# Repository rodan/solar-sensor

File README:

Solar sensor device that implements the following:

   - read temperature, humidity, pressure and geiger counter sensors
   - read thermocouple temperature
   - read and set alarms in the real time clock
   - log sensor data on a microSD card
   - control room heating or cooling via RF power switches
   - use a communication protocol to send data to a PC

  there are 4 components in this repository:
  firmware_arduino  - contains the Arduino source code (avr version)
  firmware_avr      - stand-alone source code (avr version)
  hardware_avr      - open source hardware for the main board (avr version)
  server            - server-side implementation of the comm protocol

  pictures of rev02 and rev03 are available at 
            https://picasaweb.google.com/petre.rodan/SolarSensor

  Library dependencies for firmware_arduino software:

  ds3231      https://github.com/rodan/ds3231
  max6675     https://github.com/rodan/max6675
  bmp085      https://github.com/rodan/bmp085
  sht15       http://www.arduino.cc/playground/Code/Sensirion
  IRremote    https://github.com/shirriff/Arduino-IRremote
  SDfatlib    http://code.google.com/p/sdfatlib/

  dependencies for the server-side software:

  linux with working ftdi kernel driver
  sqlite      http://www.sqlite.org/
  gnuplot     http://www.gnuplot.info/

  Hardware needed:

  SHT15 Humidity and Temperature Sensor  - sparkfun sku: SEN-08257
  Grove - Geiger Counter - seeed studio sku: SEN63024P
  3W Solar Panel  - seeed studio sku: POW92136O
  Lithium Ion polymer Battery - 2Ah 3.7V  - seeed studio sku: POW103C1P
  XBee 2mW Chip Antenna - Series 2 ZigBee (2 pcs)  - sparkfun sku: WRL-10415
  XBee Explorer USB  - sparkfun sku: WRL-08687
  main board that includes the LiPo charger, DS3231 to wake up the system, 
    5v boost, one logic level converter, 3.3v stabilized sources, atmega328p uC, 
    uSD card socket, xbee socket, digital cold junction compensated K-type 
    thermocouple IC and mosfets to power off unused modules.

  How does it work

    Power: the main power is from a 2Ah LiPo cell that is charged from the solar panel. a stabilization circuit and a boost give out 3.3V and 5V respectively. a small coin cell battery keeps the DS3231 RTC chip working at all times. the RTC's alarm function is waking up the microcontroller once every 30 minutes.

    Sensors: some are internal and some kept outside. The outside temperature and humidity are measured by a SHT15 chip. the Geiger-Muller tube is also kept outside. the internal temperature is read from the RTC chip, or via a K-type thermocouple.

    Sensor data: is saved to a uSD card and if the receiving PC is up and if the wireless signal haven't got too much interference than a protocol is used to send new data to the PC. it ends up here: http://www.simplex.ro/ro/statie_meteo.html

    Commands: are being given either via the wireless serial interface or via a universal remote control that can speak RC5 (most remotes can).

  Author:          Petre Rodan <2b4eda@subdimension.ro>
  Available from:  https://github.com/rodan/solar-sensor
  License:         GNU GPLv3

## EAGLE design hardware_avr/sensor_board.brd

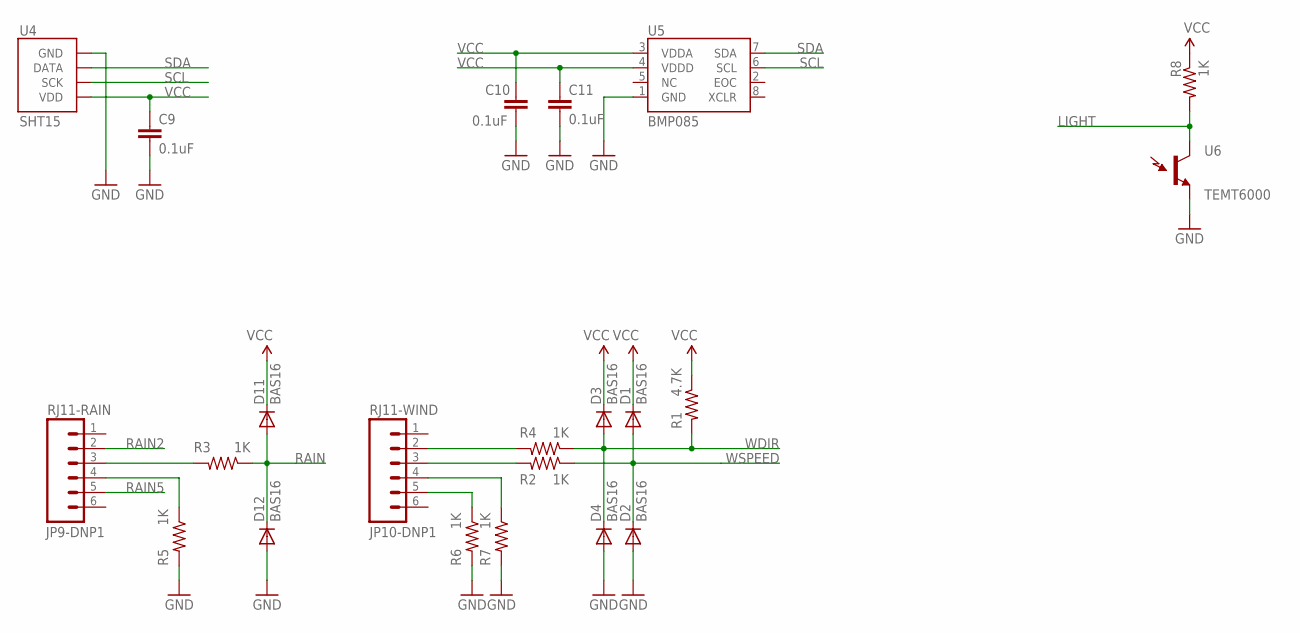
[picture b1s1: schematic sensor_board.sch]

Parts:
C9, C10, C11: 0.1uF; 0402-CAP
D1, D2, D3, D4, D11, D12: BAS16; SOD-323
JP9-DNP1: RJ11-RAIN; RJ11-6
JP10-DNP1: RJ11-WIND; RJ11-6
R1: 4.7K; 0402-RES
R2, R3, R4, R5, R6, R7, R8: 1K; 0402-RES
U4: SHT15; SHT1X
U5: BMP085
U6: TEMT6000; TEMT6000-SEN

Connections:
GND: C9.2, C10.1, C11.2, D2.2 (A), D4.2 (A), D12.2 (A), R5.2, R6.2, R7.2, U4.1 (GND), U5.1 (GND), U6.EMITTER (E1)
LIGHT: R8.2, U6.COLLECTOR (C1)
unnamed: JP10-DNP1.2, R4.2
unnamed: JP10-DNP1.3, R2.2
unnamed: JP9-DNP1.3, R3.2
unnamed: JP9-DNP1.4, R5.1
unnamed: JP10-DNP1.5, R6.1
unnamed: JP10-DNP1.4, R7.1
RAIN: D11.2 (A), D12.1 (C), R3.1
RAIN2: JP9-DNP1.2
RAIN5: JP9-DNP1.5
SCL: U4.3 (SCK), U5.6 (SCL)
SDA: U4.2 (DATA), U5.7 (SDA)
VCC: C9.1, C10.2, C11.1, D1.1 (C), D3.1 (C), D11.1 (C), R1.1, R8.1, U4.4 (VDD), U5.3 (VDDA), U5.4 (VDDD)
WDIR: D3.2 (A), D4.1 (C), R1.2, R4.1
WSPEED: D1.2 (A), D2.1 (C), R2.1

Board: 2 copper layers, 22 parts (0 on the bottom side), 14 nets, no tracks yet.

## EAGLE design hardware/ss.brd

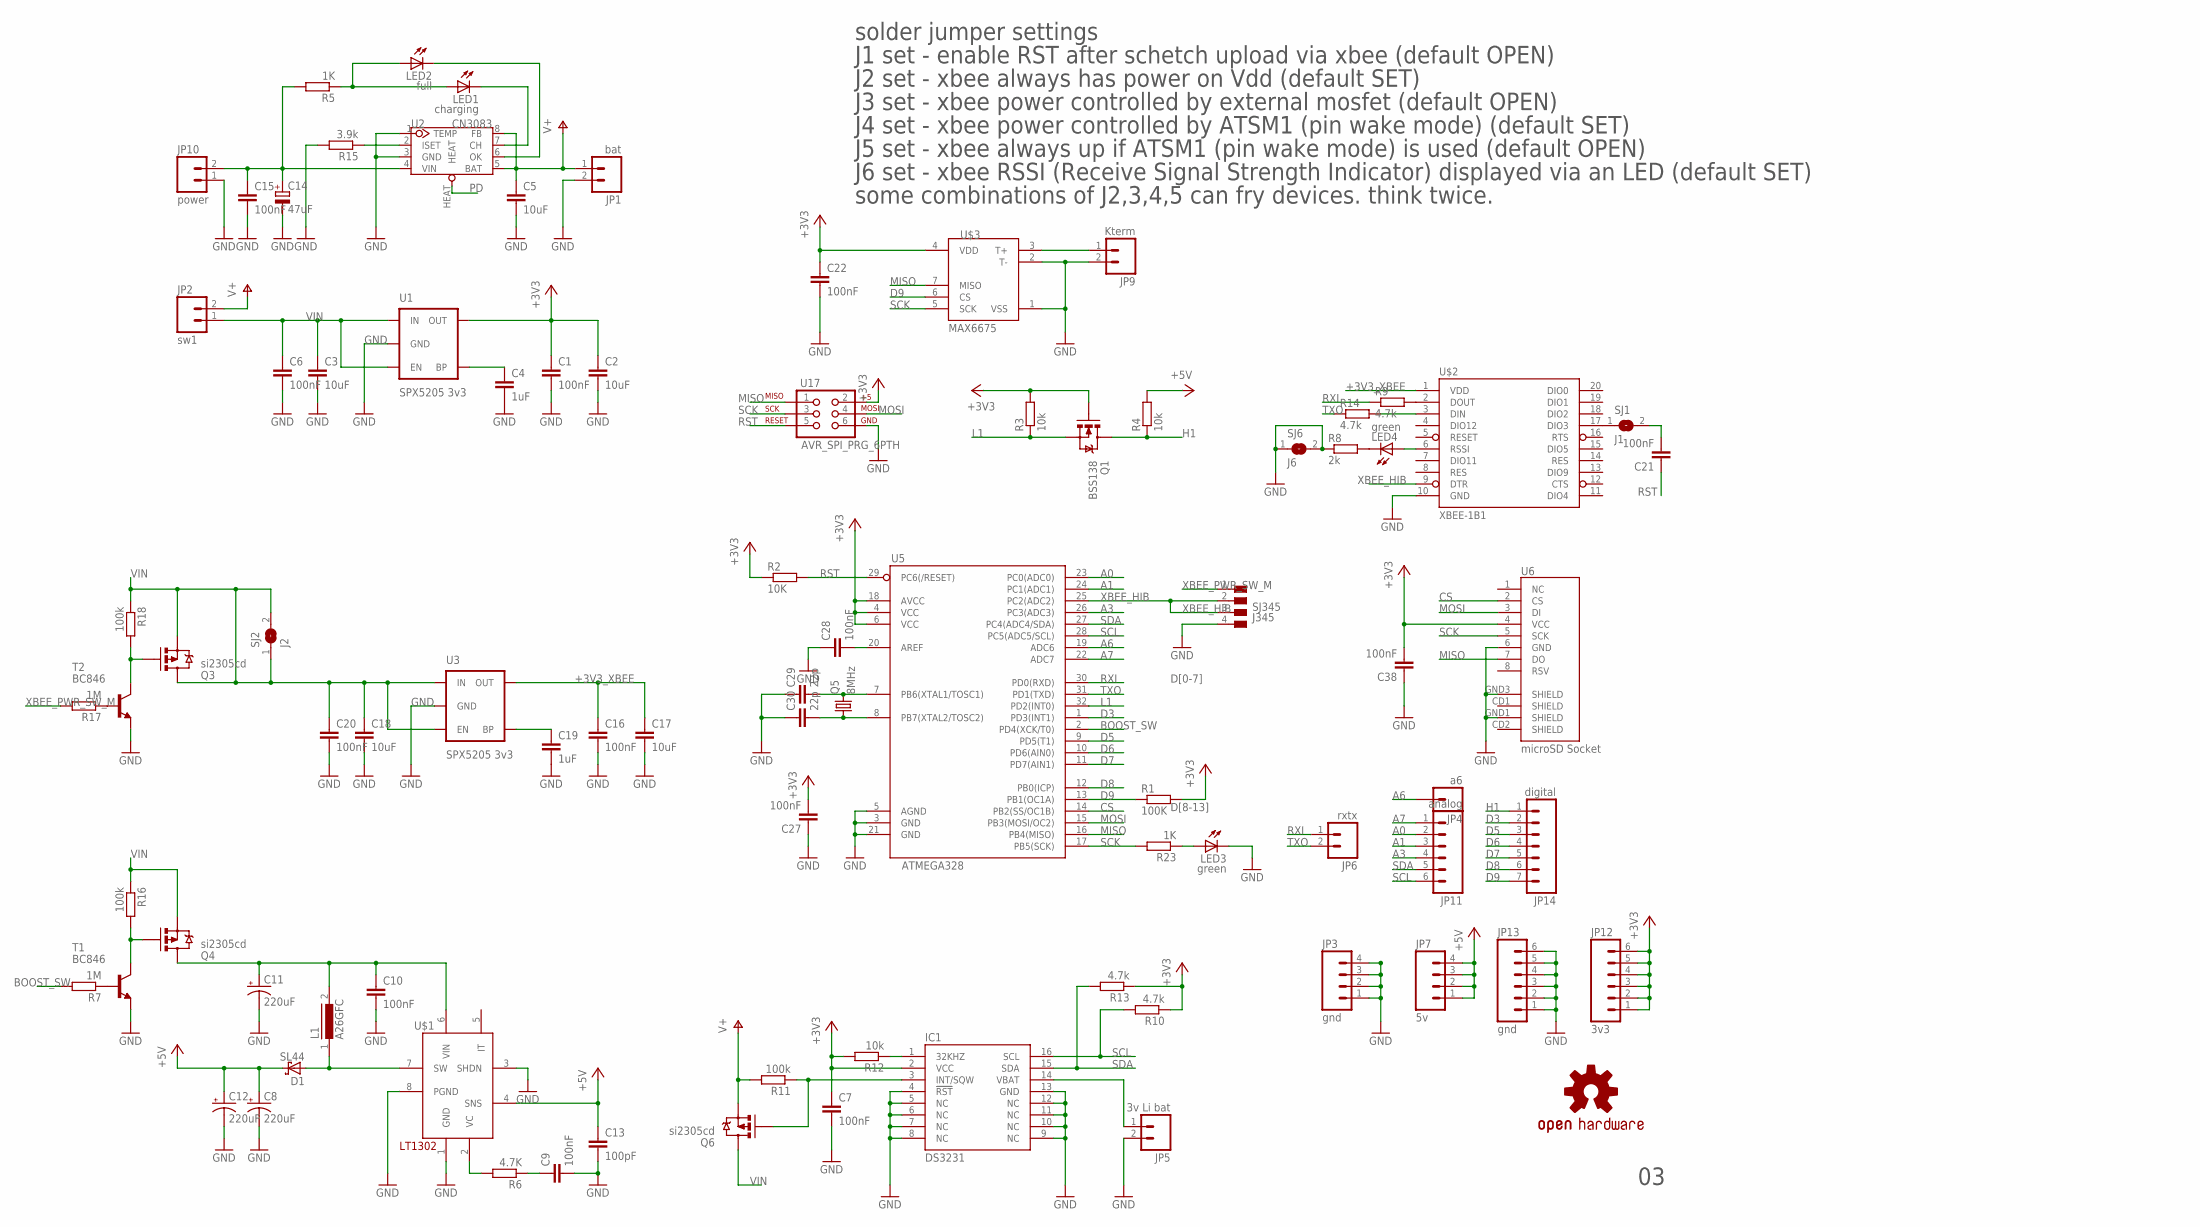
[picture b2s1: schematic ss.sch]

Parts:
C1, C6, C7, C9, C10, C15, C16, C20, C21, C22, C27, C28, C38: 100nF; C0805
C2, C3, C5, C17, C18: 10uF; C1206
C4, C19: 1uF; C0805
C8, C11, C12: 220uF; PANASONIC_D
C13: 100pF; C0805
C14: 47uF; CT7343
C29, C30: 22p; C0805
D1: SL44; SMC
IC1: DS3231; SO-16
JP1: bat; 1X02
JP2: sw1; 1X02
JP3: gnd; 1X04
JP4: a6; 1X01
JP5: 3v Li bat; 1X02
JP6: rxtx; 1X02
JP7: 5v; 1X04
JP9: Kterm; 1X02
JP10: power; 1X02
JP11: analog; 1X06
JP12: 3v3; 1X06
JP13: gnd; 1X06
JP14: digital; 1X07
L1: A26GFC
LED1: charging; CHIP-LED0805
LED2: full; CHIP-LED0805
LED3, LED4: green; CHIP-LED0805
Q1: BSS138; SOT23-3
Q3, Q4, Q6: si2305cd; SOT23-3_POWER
Q5: 8MHz; CRYSTAL_5X3.2
R1: 100K; R0805W
R2: 10K; R0805W
R3, R4, R12: 10k; R0805W
R5, R23: 1K; R0805W
R6: 4.7K; R0805W
R7, R17: 1M; R0805W
R8: 2k; R0805W
R9, R10, R13, R14: 4.7k; R0805W
R11, R16, R18: 100k; R0805W
R15: 3.9k; R0805W
SJ1: J1; SJ
SJ2: J2; SJ
SJ6: J6; SJ
SJ345: J345; SJ_4P
T1, T2: BC846; SOT23
U1, U3: SPX5205 3v3; SOT23-5
U2: CN3083; SOP8-W/-HEAT
U5: ATMEGA328; TQFP32-08
U6: microSD Socket; MICRO-SD-SOCKET-PP
U17: AVR_SPI_PRG_6PTH; 2X3
U$1: LT1302SOIC8; SO08
U$2: XBEE-1B1; XBEE-1
U$3: MAX6675; SO08-MAX6675
U$7: OSHW-LOGOM; OSHW-LOGO-M

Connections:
+3V3: C1.1, C2.1, C7.1, C22.1, C27.2, C38.2, IC1.2 (VCC), JP12.1, JP12.2, JP12.3, JP12.4, JP12.5, JP12.6, Q1.1 (G), R1.2, R2.1, R3.2, R10.1, R12.2, R13.1, U1.5 (OUT), U5.4 (VCC), U5.6 (VCC), U5.18 (AVCC), U6.4 (VCC), U17.2, U$3.4 (VDD)
+3V3_XBEE: C16.1, C17.1, U3.5 (OUT), U$2.1 (VDD)
+5V: C8.+, C12.+, C13.1, D1.C, JP7.1, JP7.2, JP7.3, JP7.4, R4.2, U$1.4 (SNS)
A0: JP11.2, U5.23 (PC0(ADC0))
A1: JP11.3, U5.24 (PC1(ADC1))
A3: JP11.4, U5.26 (PC3(ADC3))
A6: JP4.1, U5.19 (ADC6)
A7: JP11.1, U5.22 (ADC7)
BOOST_IN: C10.1, C11.+, L1.2, Q4.3 (D), U$1.6 (VIN)
BOOST_SW: R7.2, U5.2 (PD4(XCK/T0))
CS: U5.14 (PB2(SS/OC1B)), U6.2 (CS)
D3: JP14.2, U5.1 (PD3(INT1))
D5: JP14.3, U5.9 (PD5(T1))
D6: JP14.4, U5.10 (PD6(AIN0))
D7: JP14.5, U5.11 (PD7(AIN1))
D8: JP14.6, U5.12 (PB0(ICP))
D9: JP14.7, R1.1, U5.13 (PB1(OC1A)), U$3.6 (CS)
GND: C1.2, C2.2, C3.2, C4.2, C5.2, C6.2, C7.2, C8.-, C9.2, C10.2, C11.-, C12.-, C13.2, C14.-, C15.2, C16.2, C17.2, C18.2, C19.2, C20.2, C22.2, C27.1, C28.1, C29.1, C30.1, C38.1, IC1.4 (!RST), IC1.5 (NC), IC1.6 (NC), IC1.7 (NC), IC1.8 (NC), IC1.9 (NC), IC1.10 (NC), IC1.11 (NC), IC1.12 (NC), IC1.13 (GND), JP1.2, JP3.1, JP3.2, JP3.3, JP3.4, JP5.2, JP9.2, JP10.1, JP13.1, JP13.2, JP13.3, JP13.4, JP13.5, JP13.6, LED3.C, R8.1, R15.2, SJ6.1, SJ6.2, SJ345.4, T1.2 (E), T2.2 (E), U1.2 (GND), U2.1 (TEMP), U2.3 (GND), U3.2 (GND), U5.3 (GND), U5.5 (AGND), U5.21 (GND), U6.6 (GND), U6.GND1 (SHIELD), U6.GND3 (SHIELD), U17.6, U$1.1 (GND), U$1.3 (SHDN), U$1.8 (PGND), U$2.10 (GND), U$3.1 (VSS), U$3.2 (T-)
H1: JP14.1, Q1.3 (D), R4.1
L1: Q1.2 (S), R3.1, U5.32 (PD2(INT0))
MISO: U5.16 (PB4(MISO)), U6.7 (DO), U17.1, U$3.7 (MISO)
MOSI: U5.15 (PB3(MOSI/OC2)), U6.3 (DI), U17.4
unnamed: IC1.3 (INT/SQW), Q6.1 (G), R11.1
unnamed: C4.1, U1.4 (BP)
unnamed: D1.A, L1.1, U$1.7 (SW)
unnamed: SJ1.1, U$2.17 (DIO3)
unnamed: C19.1, U3.4 (BP)
unnamed: LED4.C, R8.2
unnamed: LED4.A, U$2.6 (RSSI)
unnamed: IC1.1 (32KHZ), R12.1
unnamed: R15.1, U2.2 (ISET)
unnamed: IC1.14 (VBAT), JP5.1
unnamed: R6.2, U$1.2 (VC)
unnamed: C14.+, C15.1, JP10.2, R5.2, U2.4 (VIN)
unnamed: C9.1, R6.1
unnamed: LED1.A, LED2.A, R5.1
unnamed: LED1.C, U2.7 (CH)
unnamed: LED2.C, U2.6 (OK)
unnamed: C21.2, SJ1.2
unnamed: R17.1, T2.1 (B)
unnamed: C30.2, Q5.P$1 (1), U5.8 (PB7(XTAL2/TOSC2))
unnamed: Q3.1 (G), R18.2, T2.3 (C)
unnamed: C29.2, Q5.P$2 (2), U5.7 (PB6(XTAL1/TOSC1))
unnamed: C28.2, U5.20 (AREF)
unnamed: R9.2, U$2.2 (DOUT)
unnamed: R14.2, U$2.3 (DIN)
unnamed: R7.1, T1.1 (B)
unnamed: Q4.1 (G), R16.2, T1.3 (C)
unnamed: LED3.A, R23.1
PD: U2.HEAT
RST: C21.1, R2.2, U5.29 (PC6(/RESET)), U17.5
RXI: JP6.1, R9.1, U5.30 (PD0(RXD))
SCK: R23.2, U5.17 (PB5(SCK)), U6.5 (SCK), U17.3, U$3.5 (SCK)
SCL: IC1.16 (SCL), JP11.6, R10.2, U5.28 (PC5(ADC5/SCL))
SDA: IC1.15 (SDA), JP11.5, R13.2, U5.27 (PC4(ADC4/SDA))
T+: JP9.1, U$3.3 (T+)
TXO: JP6.2, R14.1, U5.31 (PD1(TXD))
V+: C5.1, JP1.1, JP2.2, Q6.2 (S), R11.2, U2.5 (BAT), U2.8 (FB)
VIN: C3.1, C6.1, C18.1, C20.1, JP2.1, Q3.2 (S), Q3.3 (D), Q4.2 (S), Q6.3 (D), R16.1, R18.1, SJ2.1, SJ2.2, U1.1 (IN), U1.3 (EN), U3.1 (IN), U3.3 (EN)
XBEE_HIB: SJ345.2, SJ345.3, U5.25 (PC2(ADC2)), U$2.9 (DTR)
XBEE_PWR_SW_M: R17.2, SJ345.1

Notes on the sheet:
D[0-7]
D[8-13]
J1 set - enable RST after schetch upload via xbee (default OPEN)
J2 set - xbee always has power on Vdd (default SET)
solder jumper settings
J3 set - xbee power controlled by external mosfet (default OPEN)
J4 set - xbee power controlled by ATSM1 (pin wake mode) (default SET)
J5 set - xbee always up if ATSM1 (pin wake mode) is used (default OPEN)
J6 set - xbee RSSI (Receive Signal Strength Indicator) displayed via an LED (default SET)
some combinations of J2,3,4,5 can fry devices. think twice.

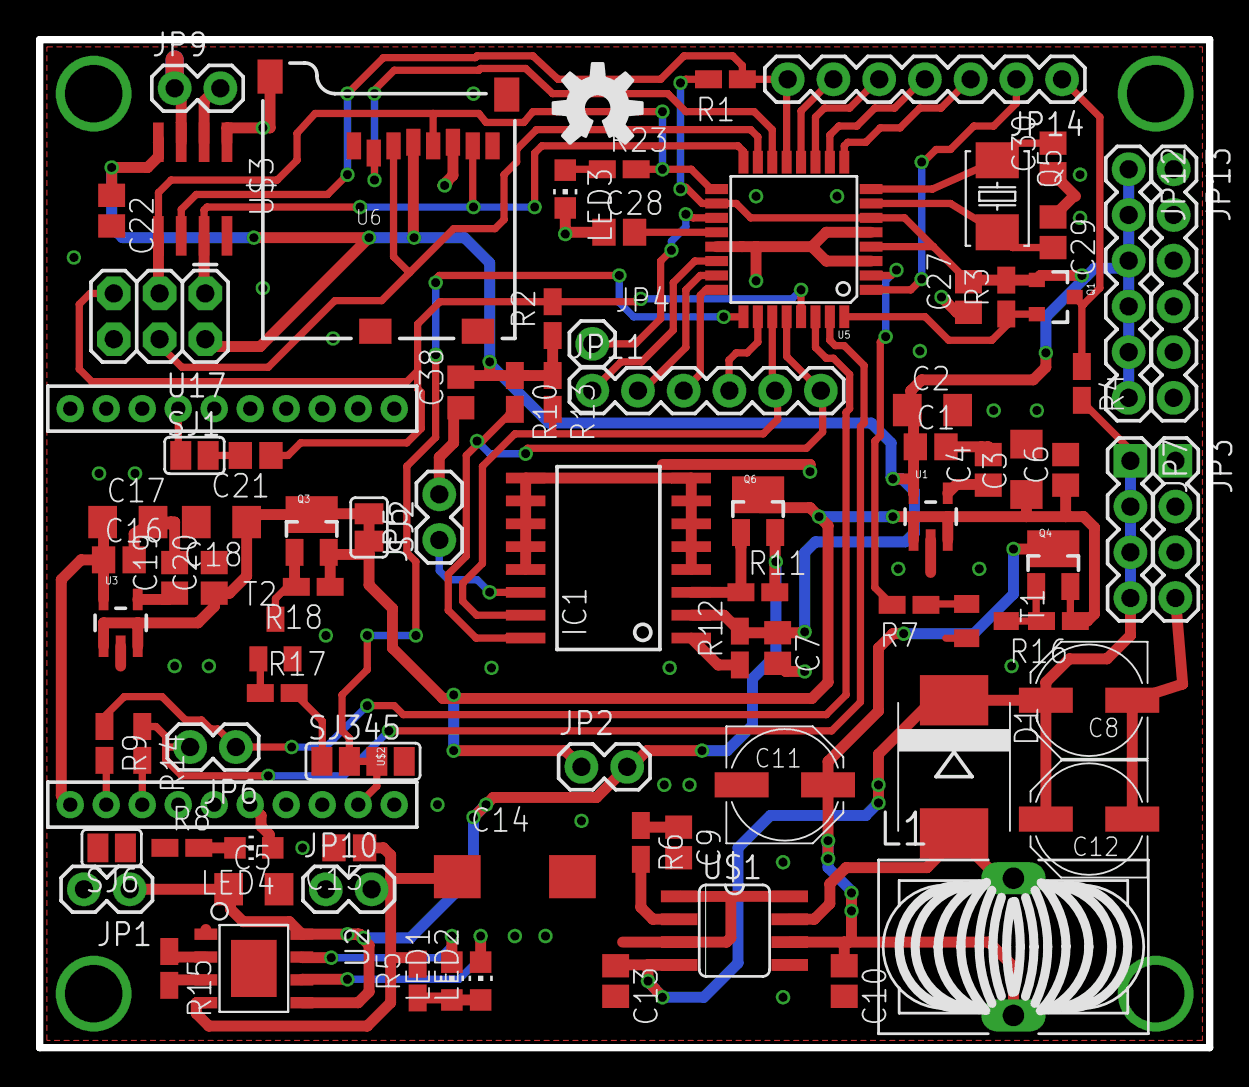
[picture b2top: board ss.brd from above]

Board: 2 copper layers, 65.0 x 56.0 mm, 87 parts (0 on the bottom side), 60 nets.

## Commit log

2011-12-07 initial import
2011-12-09 cleanup
2011-12-12 GET NOW now also gets an OK suffix
2011-12-12 if GET NOW worked ok all day long, don't read the current day from the card
2011-12-17 use hibernation pin on the ZigBee
2011-12-21 implement HALT command
2012-01-10 arduino 1.0 compatibility
2012-01-10 README added
2012-01-10 wrapping fixed
2012-02-14 switch to rev03
2012-02-14 rev03 of the avr code
2012-02-14 removed cruft
2012-02-15 here comes the xml
2012-02-15 ss board rev03. draft
2012-02-15 documentation update for rev03
2012-03-13 latest
2012-03-18 the come back of the jumpers
2012-03-18 hopefully flawless
2012-03-18 rev03 sent to manufacture
2012-03-25 rev03 related pin reassignments
2012-04-07 d9 needs external weak pullup during programming
2012-04-07 yay, boost switch
2012-04-07 thermocouple t- must be grounded
2012-04-09 move power socket
2012-04-09 add max6675 related code
2012-04-12 data was sent too quickly for the xbee
2012-04-15 add pressure sensor
2012-04-26 combined plot added
2012-07-30 share data port A4
2012-10-13 move pde to ino
2012-10-13 add support for intertechno RF switches
2013-01-17 add config.h and hardware dependant ifdefs
2013-04-01 remove debug info
2013-07-12 add standalone avr source code
2014-12-17 add pinout
2018-09-01 email change

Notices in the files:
parts and their libraries:
SparkFun-Connectors: Licensing: CC v3.0 Share-Alike You are welcome to use this library for commercial purposes.
